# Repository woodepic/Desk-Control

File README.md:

# Desk-Control

This is a re-upload of an older project, as I didn't use github at the time. This project spanned July 2020 - August 2020. I am happy to report that it is still working perfectly to this day! (January 2022)

I personally don't enjoy having any form of light when I try to sleep. This would normally mean that I need to unplug my digital clock, monitors, etc on my desk. This causes wear on connectors, is time consuming, and certainly not elegant. To solve this problem, I created a simple relay-based PCB to toggle power on/off for various devices on my desk, and I use a simple button interface to control this. 

I also utilized an arduino to allow for smart control logic of the buttons, backlights, and relay timing. "Smart" features include a fade on/off animation in the buttons' backlights, minimum time between toggles (to allow devices to fully boot before power is cut to them), and more. The PCB uses transistor-switched 12v power to allow for a PWM signal to control the buttons' backlights, optocouplers for relay isolation protection, as well as a basic power supply. 

See below for images of the project. The far right button toggles the clock, and the middle button toggles the in-desk touch monitor:

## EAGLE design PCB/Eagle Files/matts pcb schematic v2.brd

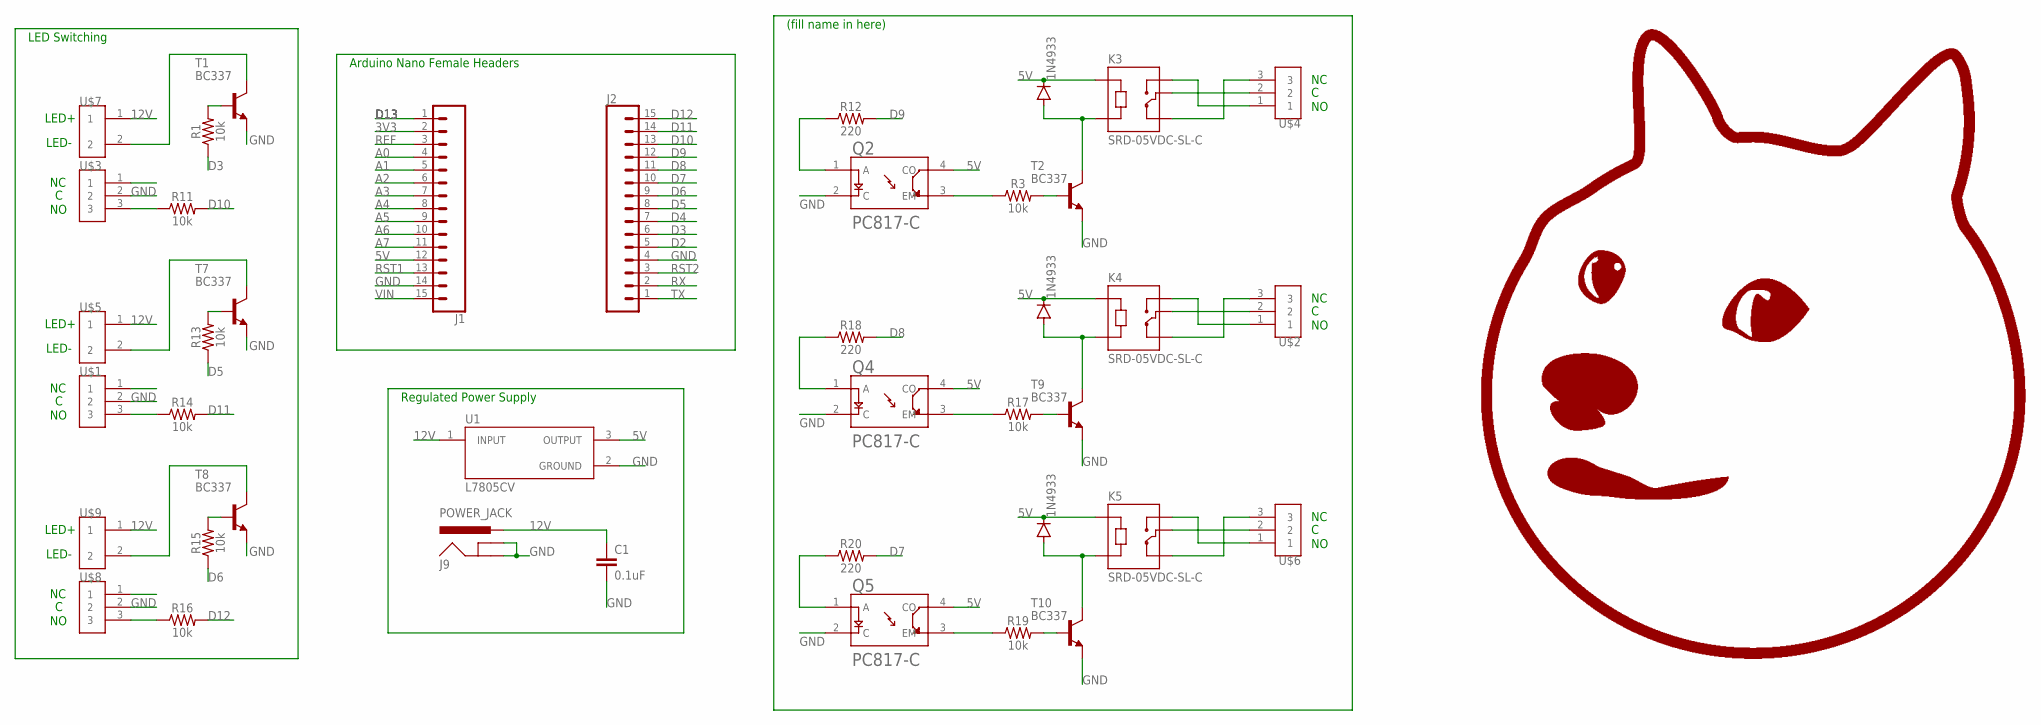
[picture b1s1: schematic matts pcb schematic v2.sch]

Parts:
C1: 0.1uF; CAP-PTH-SMALL-KIT
D1, D4, D5: 1N4933; DO41-10
J1, J2: CONN_15; 1X15
J9: POWER_JACK; POWER_JACK_PTH
K3, K4, K5: SRD-05VDC-SL-C; RELAY_SRD-05VDC-SL-C
Q2, Q4, Q5: PC817-C; DIP762W50P254L508H350Q4
R1, R3, R11, R13, R14, R15, R16, R17, R19: 10k; AXIAL-0.3
R12, R18, R20: 220; AXIAL-0.3
T1, T2, T7, T8, T9, T10: BC337; TO92
U1: L7805CV; TO255P1040X460X1968-3
U$1, U$2, U$3, U$4, U$6, U$8: 3PIN_0.2PITCH_SCREW_TERMINAL
U$5, U$7, U$9: 2PIN_0.2PITCH_SCREW_TERMINAL
U$10: DANK_DOGE

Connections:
3V3: J1.2
5V: D1.C, D4.C, D5.C, J1.12, K3.A1, K4.A1, K5.A1, Q2.4 (CO), Q4.4 (CO), Q5.4 (CO), U1.3 (OUTPUT)
12V: C1.1, J9.PWR, U1.1 (INPUT), U$5.1, U$7.1, U$9.1
A0: J1.4
A1: J1.5
A2: J1.6
A3: J1.7
A4: J1.8
A5: J1.9
A6: J1.10
A7: J1.11
D2: J2.5
D3: J2.6, R1.P$1 (1)
D4: J2.7
D5: J2.8, R13.P$1 (1)
D6: J2.9, R15.P$1 (1)
D7: J2.10, R20.P$2 (2)
D8: J2.11, R18.P$2 (2)
D9: J2.12, R12.P$2 (2)
D10: J2.13, R11.P$2 (2)
D11: J2.14, R14.P$2 (2)
D12: J2.15, R16.P$2 (2)
D13: J1.1
GND: C1.2, J1.14, J2.4, J9.GND, J9.GNDBREAK, Q2.2 (C), Q4.2 (C), Q5.2 (C), T1.1 (E), T2.1 (E), T7.1 (E), T8.1 (E), T9.1 (E), T10.1 (E), U1.2 (GROUND), U$1.2, U$3.2, U$8.2
unnamed: K3.COM, U$4.2
unnamed: R14.P$1 (1), U$1.3
unnamed: T1.3 (C), U$7.2
unnamed: T7.3 (C), U$5.2
unnamed: R1.P$2 (2), T1.2 (B)
unnamed: R13.P$2 (2), T7.2 (B)
unnamed: R11.P$1 (1), U$3.3
unnamed: R16.P$1 (1), U$8.3
unnamed: T8.3 (C), U$9.2
unnamed: R15.P$2 (2), T8.2 (B)
unnamed: K3.NO, U$4.1
unnamed: K3.NC, U$4.3
unnamed: D1.A, K3.A2, T2.3 (C)
unnamed: R3.P$2 (2), T2.2 (B)
unnamed: Q2.3 (EM), R3.P$1 (1)
unnamed: Q2.1 (A), R12.P$1 (1)
unnamed: K4.COM, U$2.2
unnamed: K4.NO, U$2.1
unnamed: K4.NC, U$2.3
unnamed: D4.A, K4.A2, T9.3 (C)
unnamed: Q4.1 (A), R18.P$1 (1)
unnamed: R17.P$2 (2), T9.2 (B)
unnamed: Q4.3 (EM), R17.P$1 (1)
unnamed: K5.COM, U$6.2
unnamed: K5.NO, U$6.1
unnamed: K5.NC, U$6.3
unnamed: D5.A, K5.A2, T10.3 (C)
unnamed: Q5.1 (A), R20.P$1 (1)
unnamed: R19.P$2 (2), T10.2 (B)
unnamed: Q5.3 (EM), R19.P$1 (1)
REF: J1.3
RST1: J1.13
RST2: J2.3
RX: J2.2
TX: J2.1
VIN: J1.15

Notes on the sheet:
Arduino Nano Female Headers
LED+
LED-
Regulated Power Supply
LED Switching
(fill name in here)

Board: 2 copper layers, 42 parts (0 on the bottom side), 42 nets, no tracks yet.

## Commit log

2022-01-21 added images for readme
2022-01-21 Uploaded project files

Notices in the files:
parts and their libraries:
SparkFun-Connectors: Licensing: Creative Commons ShareAlike 4.0 International - https://creativecommons.org/licenses/by-sa/4.0
